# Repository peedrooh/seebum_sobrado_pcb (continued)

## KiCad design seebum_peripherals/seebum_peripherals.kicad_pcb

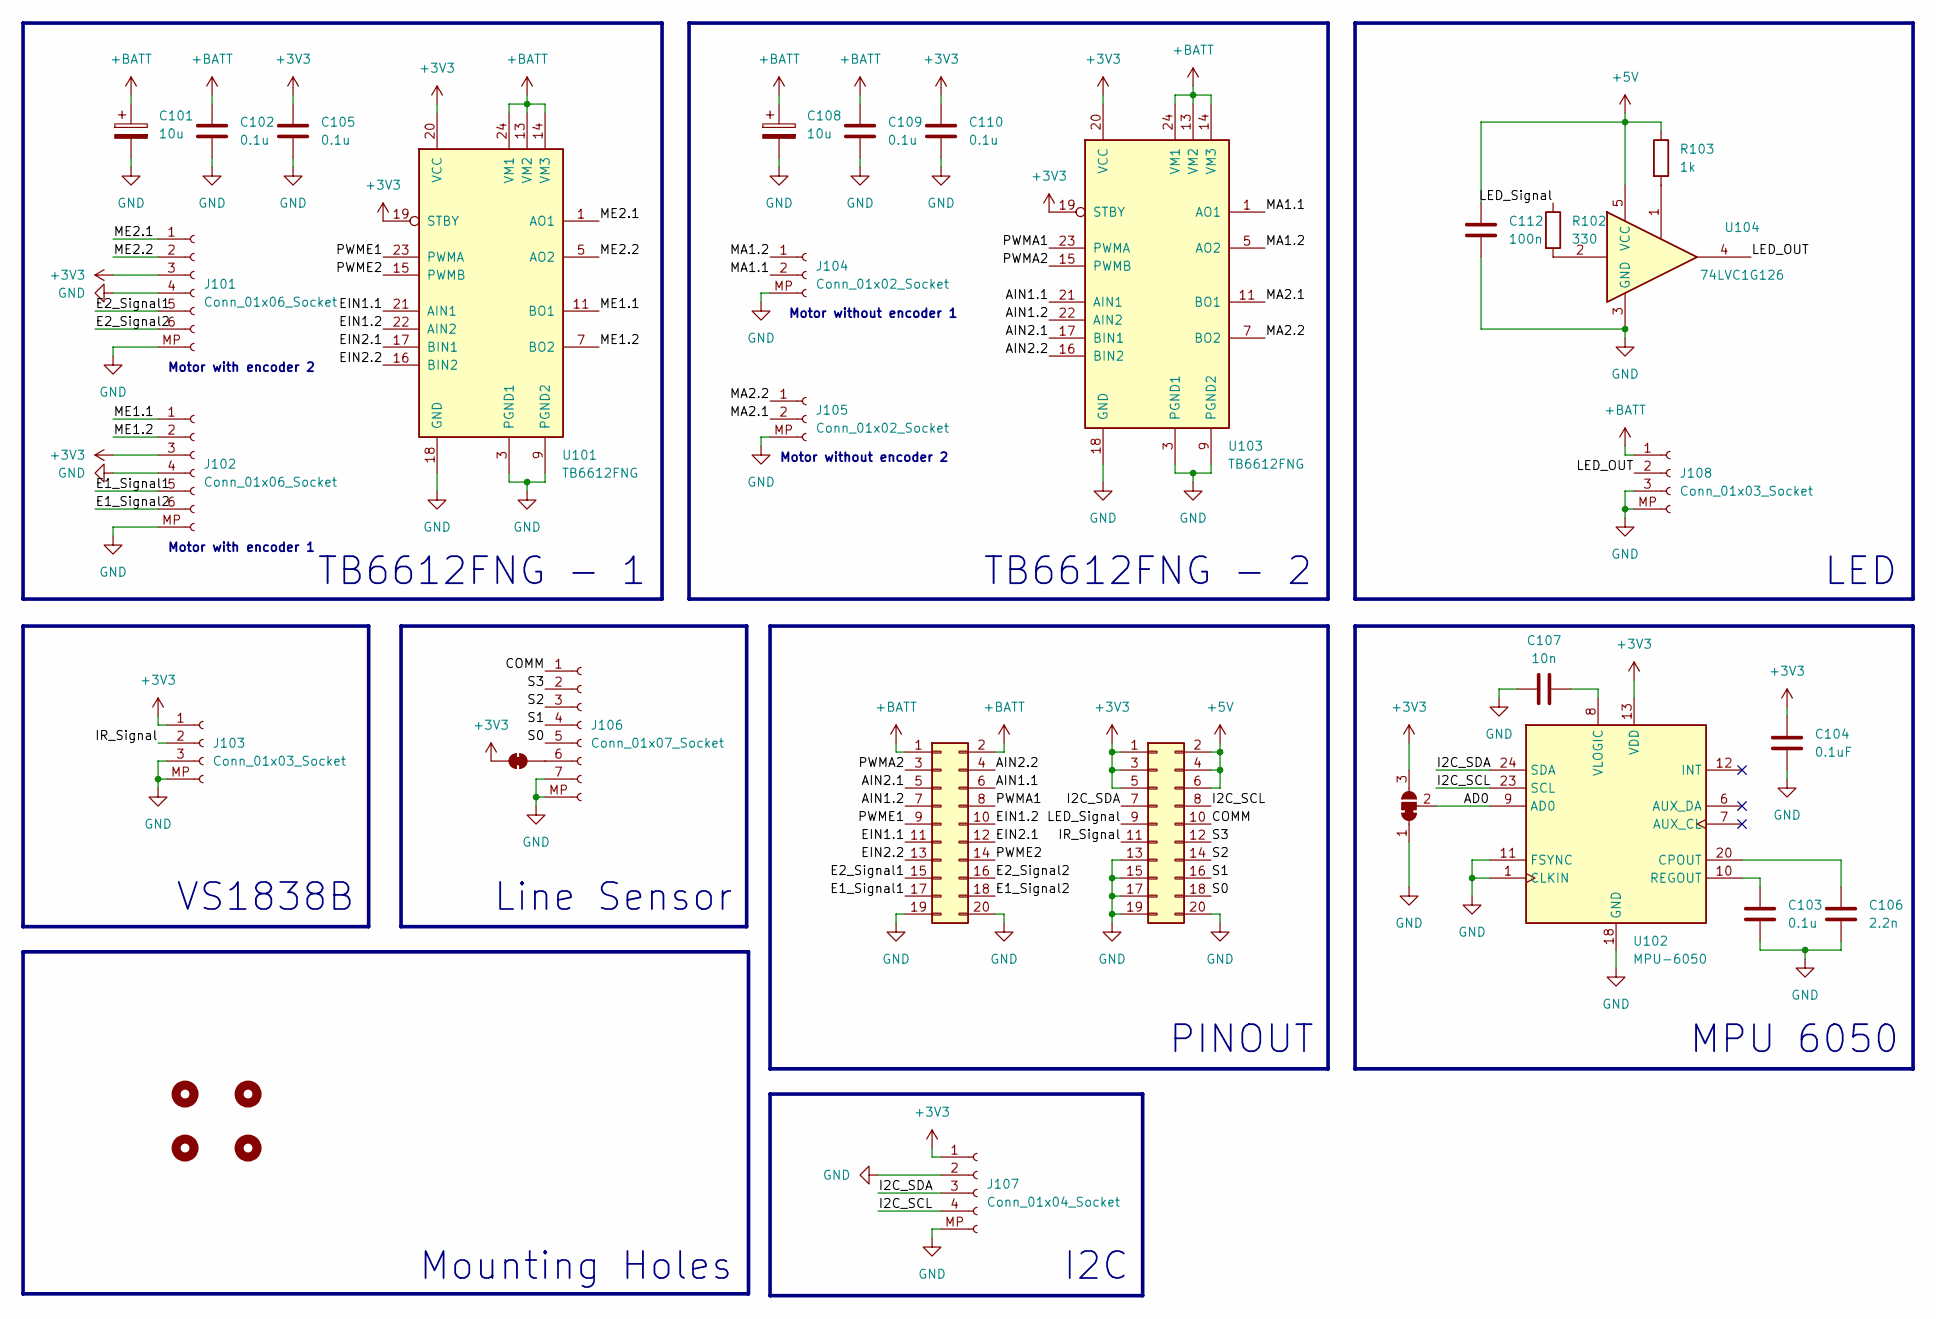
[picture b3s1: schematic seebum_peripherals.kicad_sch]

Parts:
C101, C108: 10u; CP_EIA-3528-21_Kemet-B; LCSC C163225
C102, C103, C105, C109, C110: 0.1u; C_0805_2012Metric; LCSC C38141
C104: 0.1uF; C_0805_2012Metric; LCSC C38141
C106: 2.2n; C_0805_2012Metric; LCSC C36576
C107: 10n; C_0805_2012Metric; LCSC C36576
C112: 100n; C_0805_2012Metric; LCSC C38141
H101, H102, H103, H104: MountingHole; M2.5M3
J101, J102: Conn_01x06_Socket; JST_PH_B6B-PH-SM4-TB_1x06-1MP_P2.00mm_Vertical; LCSC C265088
J103, J108: Conn_01x03_Socket; JST_PH_B3B-PH-SM4-TB_1x03-1MP_P2.00mm_Vertical; LCSC C160353
J104, J105: Conn_01x02_Socket; JST_PH_B2B-PH-SM4-TB_1x02-1MP_P2.00mm_Vertical; LCSC C160352
J106: Conn_01x07_Socket; JST_PH_B7B-PH-SM4-TB_1x07-1MP_P2.00mm_Vertical; LCSC C495700
J107: Conn_01x04_Socket; JST_PH_B4B-PH-SM4-TB_1x04-1MP_P2.00mm_Vertical
J109, J110: Conn_02x10_Odd_Even; PinSocket_2x10_P2.54mm_Vertical
JP101: SolderJumper_3_Bridged12; SolderJumper-3_P1.3mm_Bridged12_RoundedPad1.0x1.5mm
JP102: SolderJumper_2_Bridged; SolderJumper-2_P1.3mm_Bridged_RoundedPad1.0x1.5mm
R102: 330; R_0805_2012Metric; LCSC C17630
R103: 1k; R_0805_2012Metric; LCSC C17513
U101, U103: TB6612FNG; SSOP-24_5.3x8.2mm_P0.65mm; LCSC C88224
U102: MPU-6050; InvenSense_QFN-24_4x4mm_P0.5mm; LCSC C24112
U104: 74LVC1G126; SOT-23-5; LCSC C7834

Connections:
+3V3: C104.1, C105.1, C110.1, J101.3, J102.3, J103.1, J107.1, J110.1, J110.3, J110.5, JP101.3 (B), JP102.1 (A), U101.19 (STBY), U101.20 (VCC), U102.13 (VDD), U103.19 (STBY), U103.20 (VCC)
+5V: C112.1, J110.2, J110.4, J110.6, R103.1, U104.5 (VCC)
+BATT: C101.1, C102.1, C108.1, C109.1, J108.1, J109.1, J109.2, U101.13 (VM2), U101.14 (VM3), U101.24 (VM1), U103.13 (VM2), U103.14 (VM3), U103.24 (VM1)
/AD0: JP101.2 (C), U102.9 (AD0)
/AIN1.1: J109.6, U103.21 (AIN1)
/AIN1.2: J109.7, U103.22 (AIN2)
/AIN2.1: J109.5, U103.17 (BIN1)
/AIN2.2: J109.4, U103.16 (BIN2)
/COMM: J106.1, J110.10
/E1_Signal1: J102.5, J109.17
/E1_Signal2: J102.6, J109.18
/E2_Signal1: J101.5, J109.15
/E2_Signal2: J101.6, J109.16
/EIN1.1: J109.11, U101.21 (AIN1)
/EIN1.2: J109.10, U101.22 (AIN2)
/EIN2.1: J109.12, U101.17 (BIN1)
/EIN2.2: J109.13, U101.16 (BIN2)
/I2C_SCL: J107.4, J110.8, U102.23 (SCL)
/I2C_SDA: J107.3, J110.7, U102.24 (SDA)
/IR_Signal: J103.2, J110.11
/LED_OUT: J108.2, U104.4
/LED_Signal: J110.9, R102.1
/MA1.1: J104.2, U103.1 (AO1), U103.2 (AO1)
/MA1.2: J104.1, U103.5 (AO2), U103.6 (AO2)
/MA2.1: J105.2, U103.11 (BO1), U103.12 (BO1)
/MA2.2: J105.1, U103.7 (BO2), U103.8 (BO2)
/ME1.1: J102.1, U101.11 (BO1), U101.12 (BO1)
/ME1.2: J102.2, U101.7 (BO2), U101.8 (BO2)
/ME2.1: J101.1, U101.1 (AO1), U101.2 (AO1)
/ME2.2: J101.2, U101.5 (AO2), U101.6 (AO2)
/PWMA1: J109.8, U103.23 (PWMA)
/PWMA2: J109.3, U103.15 (PWMB)
/PWME1: J109.9, U101.23 (PWMA)
/PWME2: J109.14, U101.15 (PWMB)
/S0: J106.5, J110.18
/S1: J106.4, J110.16
/S2: J106.3, J110.14
/S3: J106.2, J110.12
GND: C101.2, C102.2, C103.2, C104.2, C105.2, C106.2, C107.1, C108.2, C109.2, C110.2, C112.2, J101.4, J101.MP (Pin_7), J102.4, J102.MP (Pin_7), J103.3, J103.MP (Pin_4), J104.MP (Pin_3), J105.MP (Pin_3), J106.7, J106.MP (Pin_8), J107.2, J107.MP (Pin_5), J108.3, J108.MP (Pin_4), J109.19, J109.20, J110.13, J110.15, J110.17, J110.19, J110.20, JP101.1 (A), U101.3 (PGND1), U101.4 (PGND1), U101.9 (PGND2), U101.10 (PGND2), U101.18 (GND), U102.1 (CLKIN), U102.11 (FSYNC), U102.18 (GND), U103.3 (PGND1), U103.4 (PGND1), U103.9 (PGND2), U103.10 (PGND2), U103.18 (GND), U104.3 (GND)
unnamed: J106.6, JP102.2 (B)
unnamed: R102.2, U104.2
unnamed: R103.2, U104.1
unnamed: C106.1, U102.20 (CPOUT)
unnamed: C103.1, U102.10 (REGOUT)
unnamed: C107.2, U102.8 (VLOGIC)

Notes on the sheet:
TB6612FNG - 1
VS1838B
Motor with encoder 2
Motor with encoder 1
Mounting Holes
Motor without encoder 2
Motor without encoder 1
LED
Line Sensor
TB6612FNG - 2
MPU 6050
PINOUT
I2C

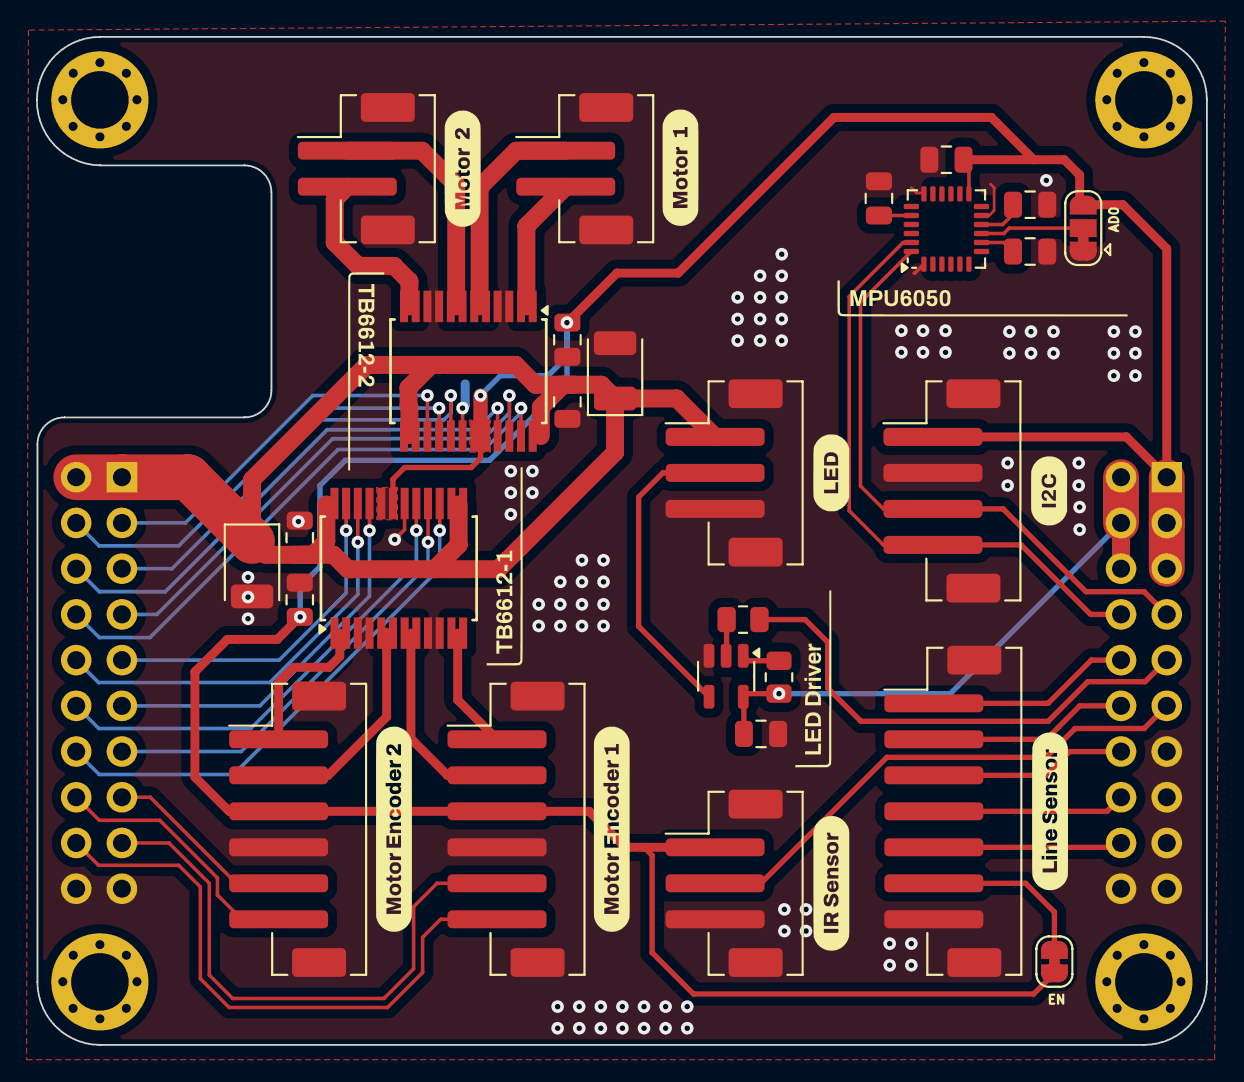
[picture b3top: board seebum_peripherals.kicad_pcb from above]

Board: 2 copper layers, 65.0 x 56.0 mm, 33 parts (0 on the bottom side), 45 nets.

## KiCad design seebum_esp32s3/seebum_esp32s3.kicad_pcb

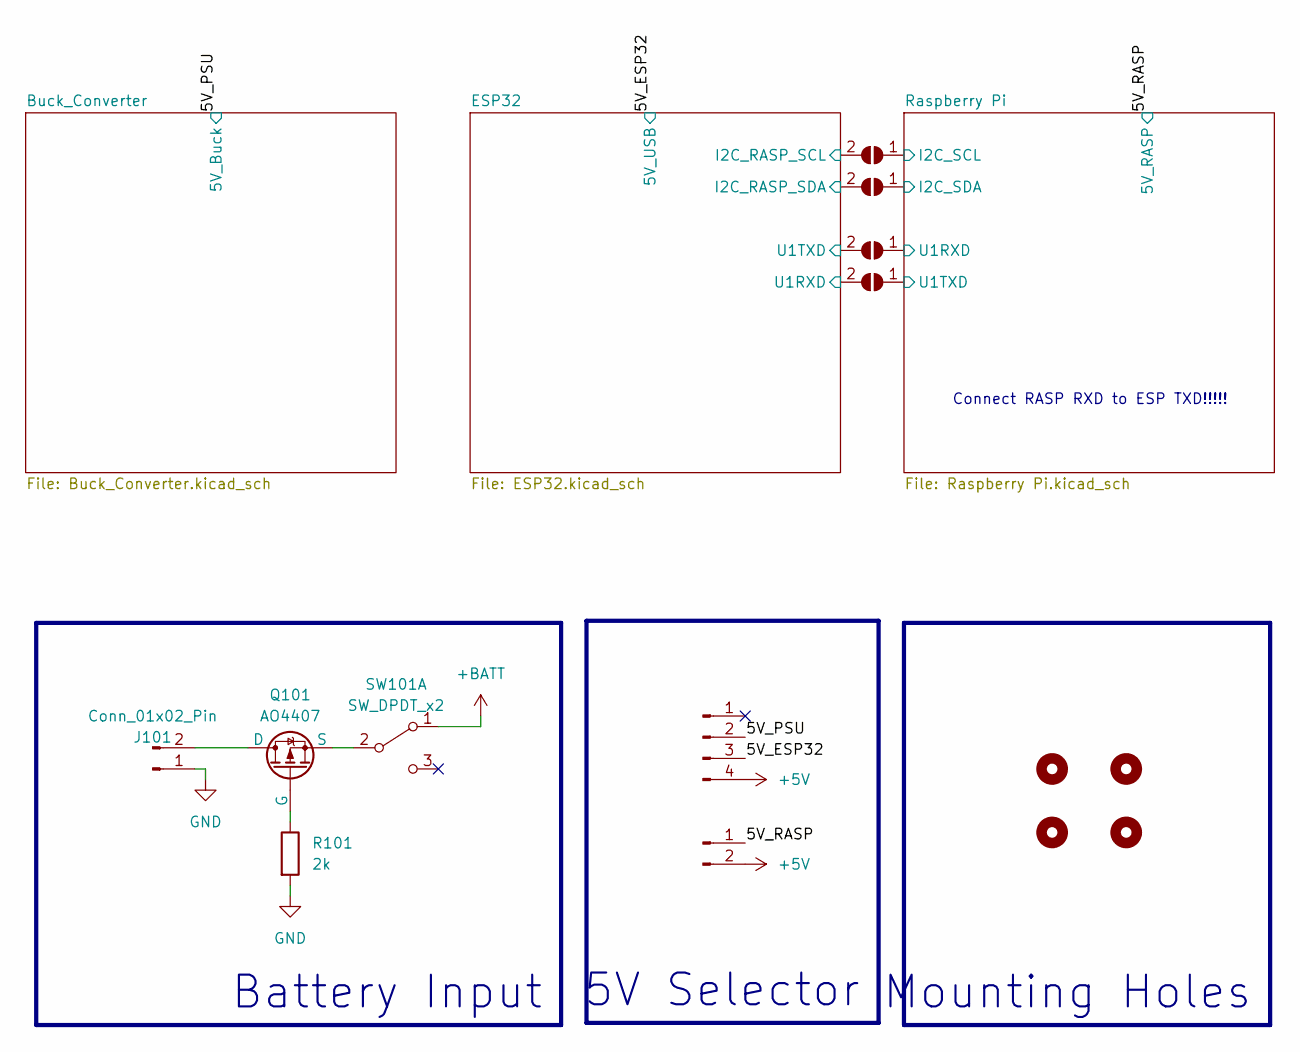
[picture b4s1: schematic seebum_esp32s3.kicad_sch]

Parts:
H101, H102, H103, H104: MountingHole; M2.5M3
J101: Conn_01x02_Pin; AMASS_XT30UPB-M_1x02_P5.0mm_Vertical
J102: Conn_01x04_Pin; PinHeader_2x02_P2.54mm_Vertical
J103: Conn_01x02_Pin; PinHeader_1x02_P2.54mm_Vertical
JP101, JP102: SolderJumper_2_Open; SolderJumper-2_P1.3mm_Open_TrianglePad1.0x1.5mm
JP103, JP104: SolderJumper_2_Open; SolderJumper-2_P1.3mm_Bridged_RoundedPad1.0x1.5mm
Q101: AO4407; SO-8_5.3x6.2mm_P1.27mm; LCSC C469397
R101: 2k; R_0805_2012Metric; LCSC C17604
SW101: SW_DPDT_x2; 5Amp_Switch; LCSC C2884744

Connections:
+5V: J102.4, J103.2; also elsewhere on the board
+BATT: SW101.1 (A); also elsewhere on the board
/5V_ESP32: J102.3; also elsewhere on the board
/5V_PSU: J102.2; also elsewhere on the board
/5V_RASP: J103.1; also elsewhere on the board
/ESP32/GPIO17: JP102.2 (B), JP103.2 (B); also elsewhere on the board
/ESP32/GPIO18: JP101.2 (B), JP104.2 (B); also elsewhere on the board
/Raspberry Pi/RASP_RX: JP103.1 (A); also elsewhere on the board
/Raspberry Pi/RASP_SCL: JP101.1 (A); also elsewhere on the board
/Raspberry Pi/RASP_SDA: JP102.1 (A); also elsewhere on the board
/Raspberry Pi/RASP_TX: JP104.1 (A); also elsewhere on the board
GND: J101.1, R101.2; also elsewhere on the board
unnamed: J101.2, Q101.1 (D)
unnamed: Q101.2 (G), R101.1
unnamed: Q101.3 (S), SW101.2 (B)

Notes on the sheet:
5V Selector
Battery Input
Mounting Holes
Connect RASP RXD to ESP TXD!!!!!

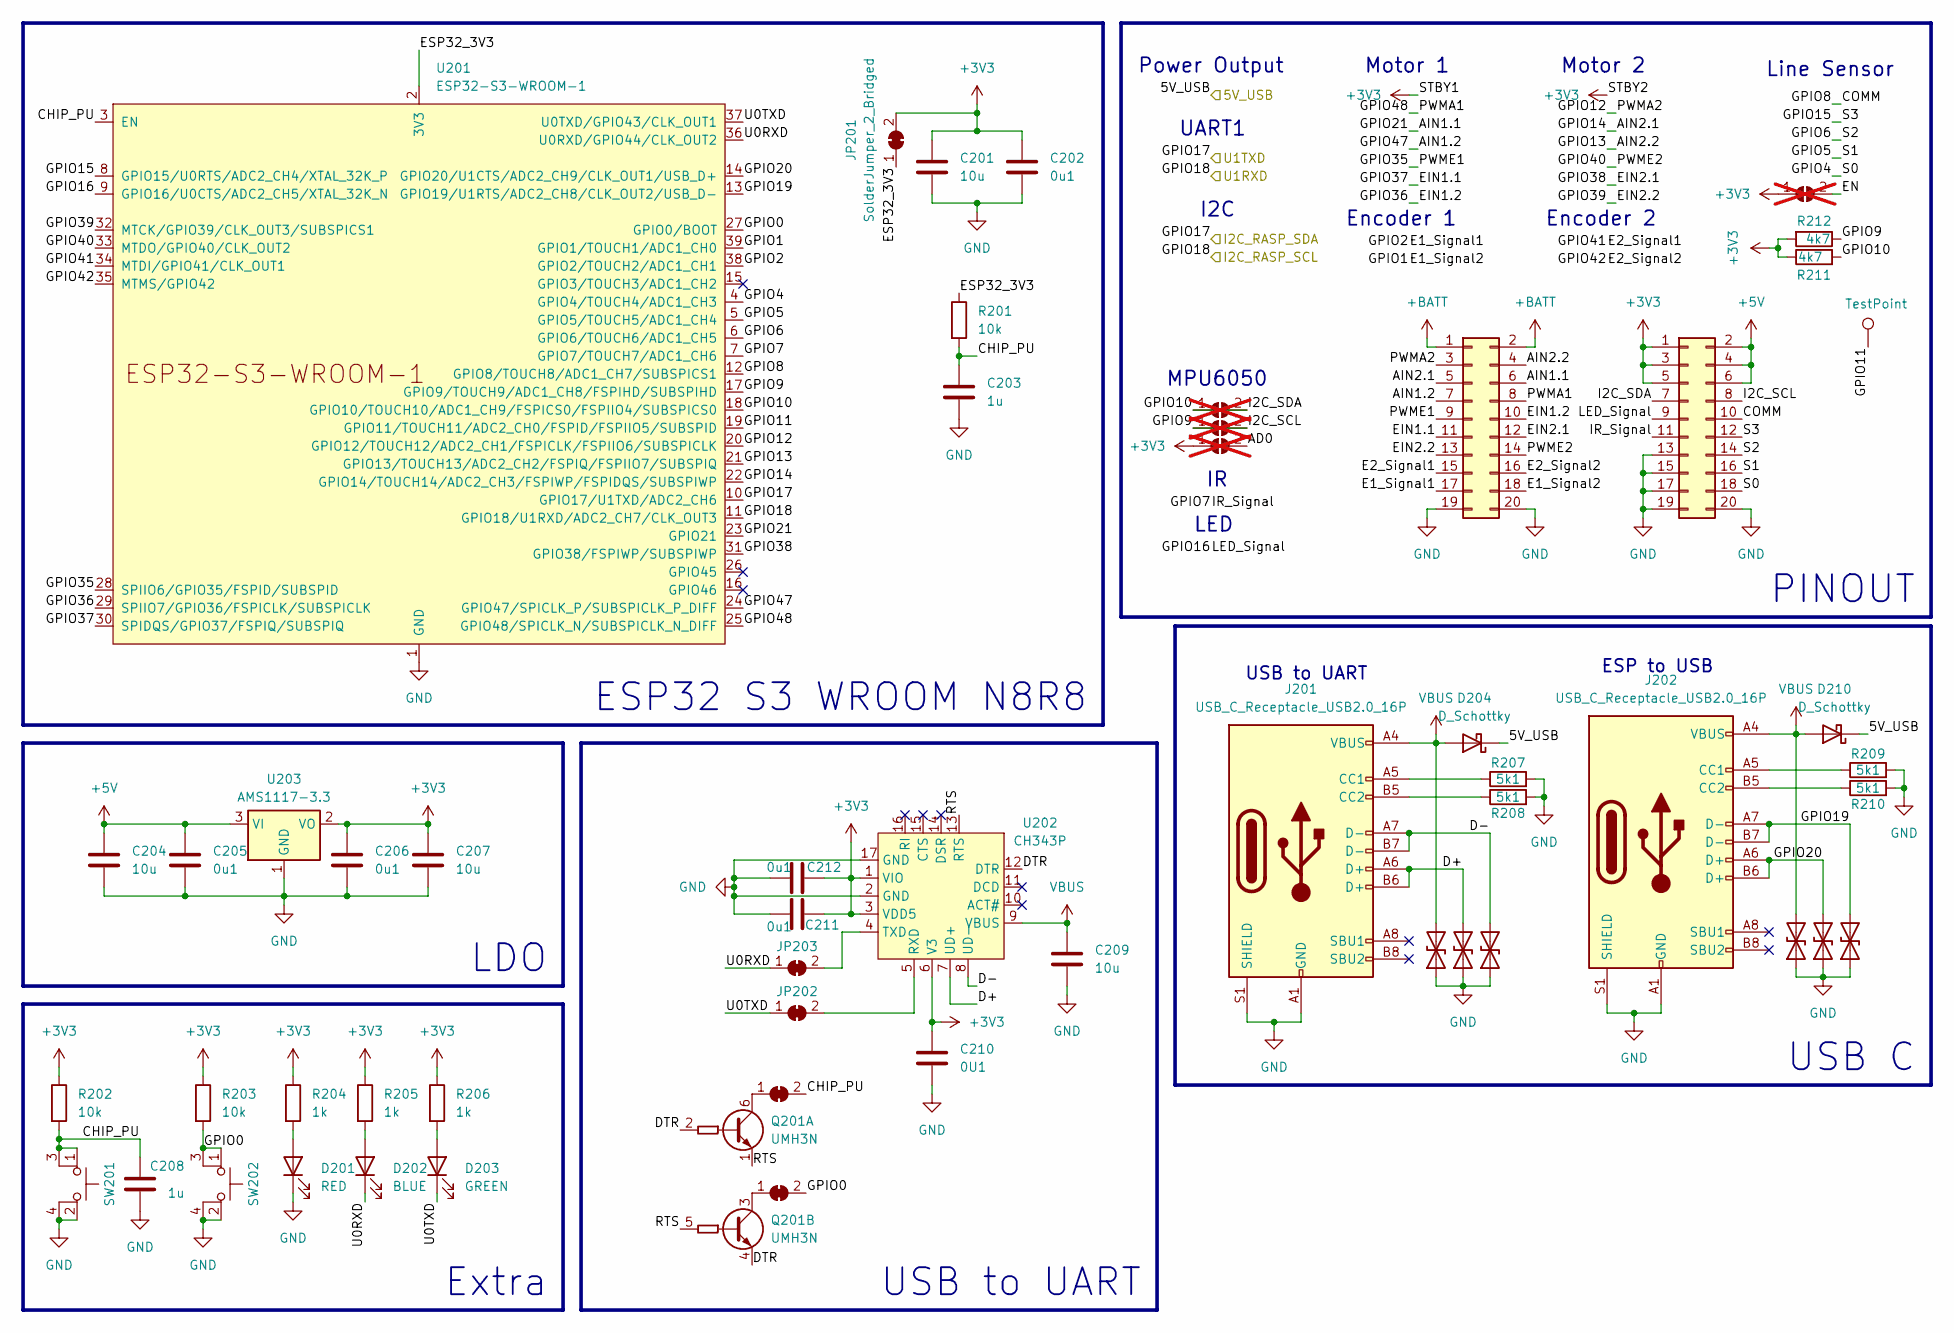
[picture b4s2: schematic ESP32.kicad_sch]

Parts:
C201, C204, C207, C209: 10u; C_0805_2012Metric_Pad1.18x1.45mm_HandSolder
C202, C205, C206, C211, C212: 0u1; C_0805_2012Metric_Pad1.18x1.45mm_HandSolder
C203, C208: 1u; C_0805_2012Metric_Pad1.18x1.45mm_HandSolder
C210: 0U1; C_0805_2012Metric_Pad1.18x1.45mm_HandSolder
D201: RED; LED_0805_2012Metric
D202: BLUE; LED_0805_2012Metric; LCSC C205441
D203: GREEN; LED_0805_2012Metric; LCSC C84260
D204, D210: D_Schottky; D_SOD-323; LCSC C2891705
D205, D206, D207, D208, D209, D211: D_TVS; D_SOD-523; LCSC C383211
J201, J202: USB_C_Receptacle_USB2.0_16P; USB_C_Receptacle_G-Switch_GT-USB-7010ASV; LCSC C2765186
J203, J204: Conn_02x10_Odd_Even; PinHeader_2x10_P2.54mm_Vertical
JP201, JP202, JP203, JP206, JP207: SolderJumper_2_Bridged; SolderJumper-2_P1.3mm_Bridged_RoundedPad1.0x1.5mm
JP204, JP205, JP208, JP209: SolderJumper_2_Open; SolderJumper-2_P1.3mm_Open_TrianglePad1.0x1.5mm; not fitted
Q201: UMH3N; SOT-363_SC-70-6; LCSC C62892
R201, R202, R203: 10k; R_0805_2012Metric_Pad1.20x1.40mm_HandSolder
R204, R205, R206: 1k; R_0805_2012Metric_Pad1.20x1.40mm_HandSolder
R207, R208, R209, R210: 5k1; R_0805_2012Metric_Pad1.20x1.40mm_HandSolder
R211, R212: 4k7; R_0805_2012Metric; LCSC C17673
SW201, SW202: SW_MEC_5E; SW_SPST_B3U-1000P; LCSC C720477
TP201: TestPoint; TestPoint_Pad_D1.0mm
U201: ESP32-S3-WROOM-1; LCSC C2913205
U202: CH343P; TQFN-16-1EP_3x3mm_P0.5mm_EP1.23x1.23mm; LCSC C2846043
U203: AMS1117-3.3; SOT-223-3_TabPin2; LCSC C347222

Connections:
+3V3: C201.1, C202.1, C206.1, C207.1, C210.1, C211.2, C212.2, J204.1, J204.3, J204.5, JP201.2 (B), JP208.1 (A), JP209.1 (A), R202.1, R203.1, R204.1, R205.1, R206.1, R211.1, R212.2, U202.1 (VIO), U202.3 (VDD5), U202.6 (V3), U203.2 (VO); also elsewhere on the board
+5V: C204.1, C205.1, J204.2, J204.4, J204.6, U203.3 (VI); also elsewhere on the board
+BATT: J203.1, J203.2; also elsewhere on the board
/5V_ESP32: D204.1 (K), D210.1 (K); also elsewhere on the board
/ESP32/AIN1.1: J203.6, U201.23 (GPIO21)
/ESP32/AIN1.2: J203.7, U201.24 (GPIO47/SPICLK_P/SUBSPICLK_P_DIFF)
/ESP32/AIN2.1: J203.5, U201.22 (GPIO14/TOUCH14/ADC2_CH3/FSPIWP/FSPIDQS/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)
/ESP32/AIN2.2: J203.4, U201.21 (GPIO13/TOUCH13/ADC2_CH2/FSPIQ/FSPIIO7/S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)
/ESP32/CHIP_PU: C203.1, C208.1, JP206.2 (B), R201.2, R202.2, SW201.1, SW201.3, U201.3 (EN)
/ESP32/COMM: J204.10, U201.12 (GPIO8/TOUCH8/ADC1_CH7/SUBSPICS1)
/ESP32/D+: D206.2 (A2), J201.A6 (D+), J201.B6 (D+), U202.7 (UD+)
/ESP32/D-: D207.2 (A2), J201.A7 (D-), J201.B7 (D-), U202.8 (UD-)
/ESP32/DTR: Q201.2 (B1), Q201.4 (E2), U202.12 (DTR)
/ESP32/E1_Signal1: J203.17, U201.38 (GPIO2/TOUCH2/ADC1_CH1)
/ESP32/E1_Signal2: J203.18, U201.39 (GPIO1/TOUCH1/ADC1_CH0)
/ESP32/E2_Signal1: J203.15, U201.34 (MTDI/GPIO41/CLK_OUT1)
/ESP32/E2_Signal2: J203.16, U201.35 (MTMS/GPIO42)
/ESP32/EIN1.1: J203.11, U201.30 (SPIDQS/GPIO37/FSPIQ/SUBSPIQ)
/ESP32/EIN1.2: J203.10, U201.29 (SPIIO7/GPIO36/FSPICLK/SUBSPICLK)
/ESP32/EIN2.1: J203.12, U201.31 (GPIO38/FSPIWP/SUBSPIWP)
/ESP32/EIN2.2: J203.13, U201.32 (MTCK/GPIO39/CLK_OUT3/SUBSPICS1)
/ESP32/ESP32_3V3: JP201.1 (A), R201.1, U201.2 (3V3)
/ESP32/GPIO0: JP207.2 (B), R203.2, SW202.1, SW202.3, U201.27 (GPIO0/BOOT)
/ESP32/GPIO4: J204.18, U201.4 (GPIO4/TOUCH4/ADC1_CH3)
/ESP32/GPIO5: J204.16, U201.5 (GPIO5/TOUCH5/ADC1_CH4)
/ESP32/GPIO6: J204.14, U201.6 (GPIO6/TOUCH6/ADC1_CH5)
/ESP32/GPIO7: J204.11, U201.7 (GPIO7/TOUCH7/ADC1_CH6)
/ESP32/GPIO9: J204.8, JP205.1 (A), JP205.2 (B), R212.1, U201.17 (GPIO9/TOUCH9/ADC1_CH8/FSPIHD/SUBSPIHD)
/ESP32/GPIO10: J204.7, JP204.1 (A), JP204.2 (B), R211.2, U201.18 (GPIO10/TOUCH10/ADC1_CH9/FSPICS0/FSPIIO4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)
/ESP32/GPIO11: TP201.1, U201.19 (GPIO11/TOUCH11/ADC2_CH0/FSPID/FSPIIO5/S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)
/ESP32/GPIO12: J203.3, U201.20 (GPIO12/TOUCH12/ADC2_CH1/FSPICLK/FSPIIO6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)
/ESP32/GPIO15: J204.12, U201.8 (GPIO15/U0RTS/ADC2_CH4/XTAL_32K_P)
/ESP32/GPIO16: J204.9, U201.9 (GPIO16/U0CTS/ADC2_CH5/XTAL_32K_N)
/ESP32/GPIO17: U201.10 (GPIO17/U1TXD/ADC2_CH6); also elsewhere on the board
/ESP32/GPIO18: U201.11 (GPIO18/U1RXD/ADC2_CH7/CLK_OUT3); also elsewhere on the board
/ESP32/GPIO19: D211.2 (A2), J202.A7 (D-), J202.B7 (D-), U201.13 (GPIO19/U1RTS/ADC2_CH8/CLK_OUT2/USB_D-)
/ESP32/GPIO20: D209.2 (A2), J202.A6 (D+), J202.B6 (D+), U201.14 (GPIO20/U1CTS/ADC2_CH9/CLK_OUT1/USB_D+)
/ESP32/GPIO35: J203.9, U201.28 (SPIIO6/GPIO35/FSPID/SUBSPID)
/ESP32/GPIO40: J203.14, U201.33 (MTDO/GPIO40/CLK_OUT2)
/ESP32/GPIO48: J203.8, U201.25 (GPIO48/SPICLK_N/SUBSPICLK_N_DIFF)
/ESP32/RTS: Q201.1 (E1), Q201.5 (B2), U202.13 (RTS)
/ESP32/U0RXD: D202.1 (K), JP203.1 (A), U201.36 (U0RXD/GPIO44/CLK_OUT2)
/ESP32/U0TXD: D203.1 (K), JP202.1 (A), U201.37 (U0TXD/GPIO43/CLK_OUT1)
GND: C201.2, C202.2, C203.2, C204.2, C205.2, C206.2, C207.2, C208.2, C209.2, C210.2, C211.1, C212.1, D201.1 (K), D205.1 (A1), D206.1 (A1), D207.1 (A1), D208.1 (A1), D209.1 (A1), D211.1 (A1), J201.A1 (GND), J201.A12 (GND), J201.B1 (GND), J201.B12 (GND), J201.S1 (SHIELD), J202.A1 (GND), J202.A12 (GND), J202.B1 (GND), J202.B12 (GND), J202.S1 (SHIELD), J203.19, J203.20, J204.13, J204.15, J204.17, J204.19, J204.20, R207.2, R208.2, R209.2, R210.2, SW201.2, SW201.4, SW202.2, SW202.4, U201.1 (GND), U201.40 (GND), U201.41 (GND), U202.2 (GND), U202.17 (GND), U203.1 (GND); also elsewhere on the board
unnamed: D201.2 (A), R204.2
unnamed: D202.2 (A), R205.2
unnamed: D203.2 (A), R206.2
unnamed: J201.A5 (CC1), R207.1
unnamed: J201.B5 (CC2), R208.1
unnamed: J202.A5 (CC1), R209.1
unnamed: J202.B5 (CC2), R210.1
unnamed: JP202.2 (B), U202.5 (RXD)
unnamed: JP203.2 (B), U202.4 (TXD)
unnamed: JP206.1 (A), Q201.6 (C1)
unnamed: JP207.1 (A), Q201.3 (C2)
VBUS: C209.1, D204.2 (A), D205.2 (A2), D208.2 (A2), D210.2 (A), J201.A4 (VBUS), J201.A9 (VBUS), J201.B4 (VBUS), J201.B9 (VBUS), J202.A4 (VBUS), J202.A9 (VBUS), J202.B4 (VBUS), J202.B9 (VBUS), U202.9 (VBUS)

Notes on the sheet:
USB to UART
UART1
Encoder 1
Line Sensor
I2C
Motor 2
PINOUT
MPU6050
USB C
ESP to USB
Motor 1
ESP32 S3 WROOM N8R8
Power Output
LED
Extra
Encoder 2
LDO

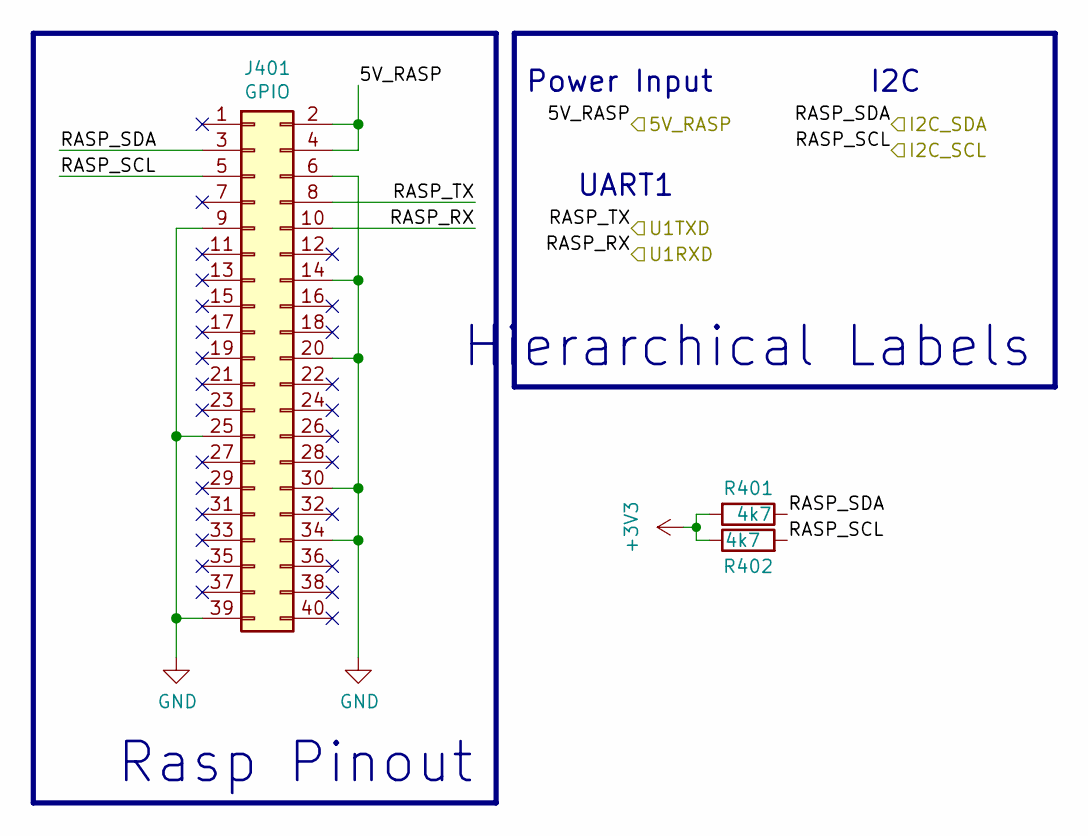
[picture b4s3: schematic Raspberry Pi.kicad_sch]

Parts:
J401: GPIO; PinSocket_2x20_P2.54mm_Vertical
R401, R402: 4k7; R_0805_2012Metric; LCSC C17673

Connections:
+3V3: R401.2, R402.1; also elsewhere on the board
/5V_RASP: J401.2, J401.4; also elsewhere on the board
/Raspberry Pi/RASP_RX: J401.10; also elsewhere on the board
/Raspberry Pi/RASP_SCL: J401.5, R402.2; also elsewhere on the board
/Raspberry Pi/RASP_SDA: J401.3, R401.1; also elsewhere on the board
/Raspberry Pi/RASP_TX: J401.8; also elsewhere on the board
GND: J401.6, J401.9, J401.14, J401.20, J401.25, J401.30, J401.34, J401.39; also elsewhere on the board

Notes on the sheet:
I2C
UART1
Rasp Pinout
Power Input
Hierarchical Labels

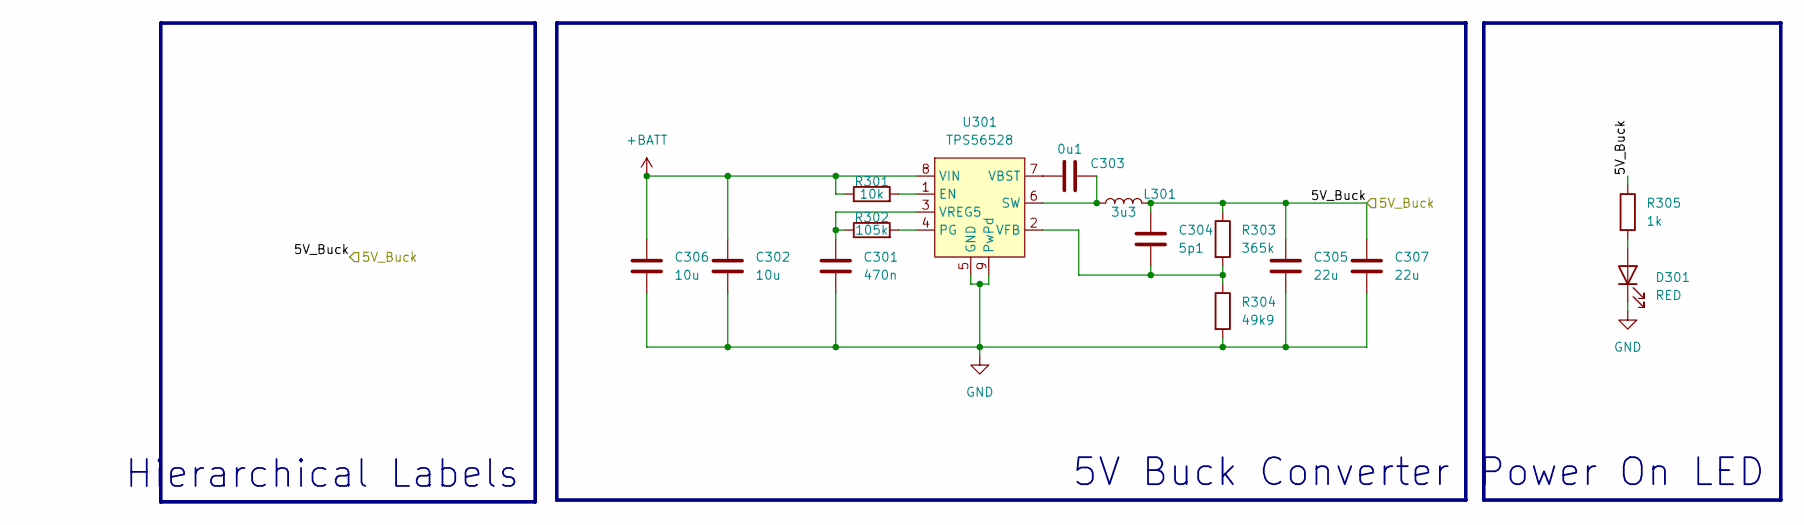
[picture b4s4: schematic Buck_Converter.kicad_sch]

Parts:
C301: 470n; C_0805_2012Metric_Pad1.18x1.45mm_HandSolder
C302: 10u; C_1210_3225Metric_Pad1.33x2.70mm_HandSolder
C303: 0u1; C_0805_2012Metric_Pad1.18x1.45mm_HandSolder
C304: 5p1; C_0805_2012Metric_Pad1.18x1.45mm_HandSolder
C305, C307: 22u; C_0805_2012Metric_Pad1.18x1.45mm_HandSolder
C306: 10u; C_1210_3225Metric_Pad1.33x2.70mm_HandSolder; LCSC C2918502
D301: RED; LED_0805_2012Metric
L301: 3u3; L_Bourns_SRP1050WA; LCSC C497894
R301: 10k; R_0805_2012Metric_Pad1.20x1.40mm_HandSolder
R302: 105k; R_0805_2012Metric_Pad1.20x1.40mm_HandSolder; LCSC C3000727
R303: 365k; R_0805_2012Metric_Pad1.20x1.40mm_HandSolder; LCSC C2999471
R304: 49k9; R_0805_2012Metric_Pad1.20x1.40mm_HandSolder; LCSC C17719
R305: 1k; R_0805_2012Metric_Pad1.20x1.40mm_HandSolder
U301: TPS56528; Texas_HSOP-8-1EP_3.9x4.9mm_P1.27mm_ThermalVias; LCSC C138716

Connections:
+BATT: C302.1, C306.1, R301.1, U301.8 (VIN); also elsewhere on the board
/5V_PSU: C304.1, C305.1, C307.1, L301.2, R303.1, R305.1; also elsewhere on the board
GND: C301.2, C302.2, C305.2, C306.2, C307.2, D301.1 (K), R304.2, U301.5 (GND), U301.9 (PwPd); also elsewhere on the board
unnamed: D301.2 (A), R305.2
unnamed: R301.2, U301.1 (EN)
unnamed: R302.2, U301.4 (PG)
unnamed: C303.2, L301.1, U301.6 (SW)
unnamed: C303.1, U301.7 (VBST)
unnamed: C304.2, R303.2, R304.1, U301.2 (VFB)
unnamed: C301.1, R302.1, U301.3 (VREG5)

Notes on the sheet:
Power On LED
5V Buck Converter
Hierarchical Labels

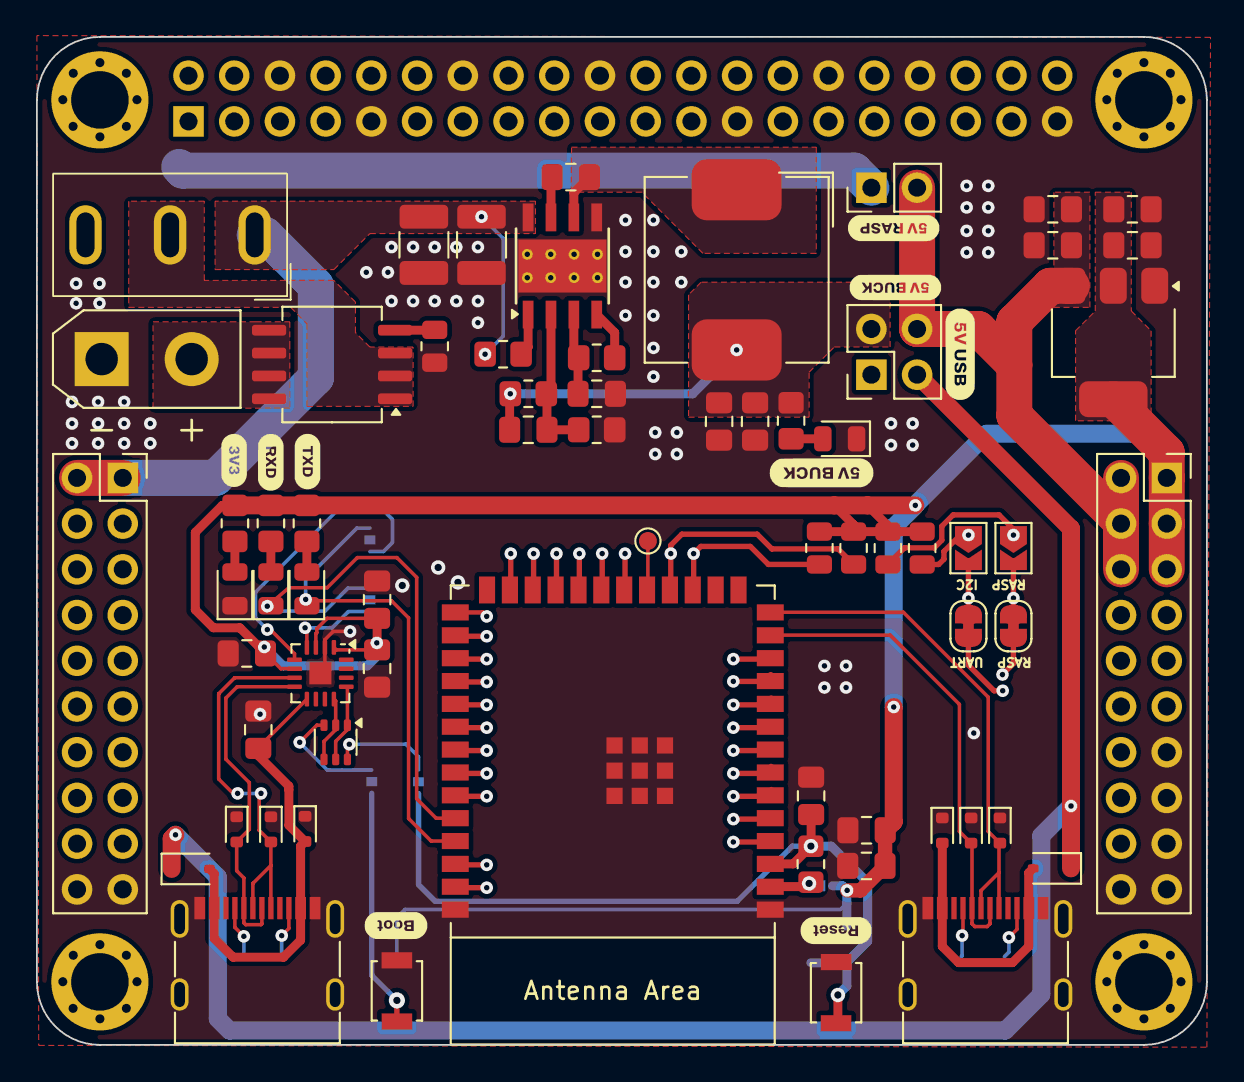
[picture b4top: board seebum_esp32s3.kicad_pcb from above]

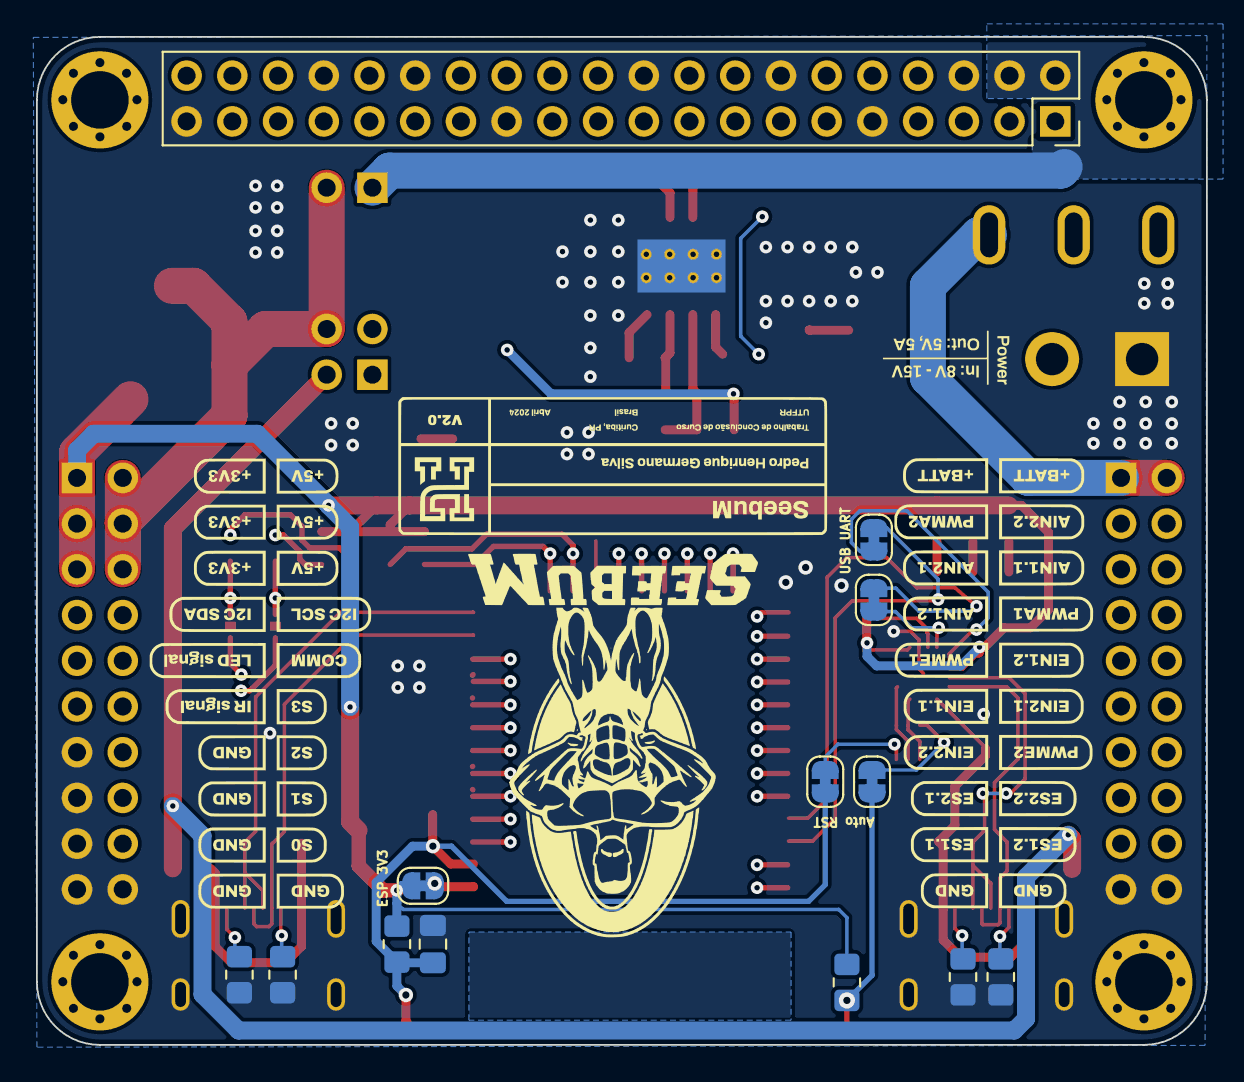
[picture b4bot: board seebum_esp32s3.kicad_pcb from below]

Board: 4 copper layers, 65.0 x 56.0 mm, 83 parts (15 on the bottom side), 72 nets.

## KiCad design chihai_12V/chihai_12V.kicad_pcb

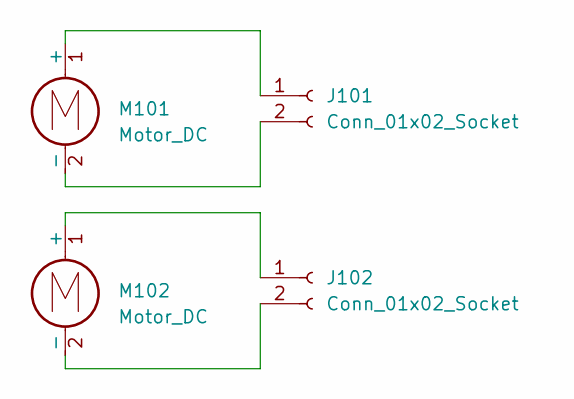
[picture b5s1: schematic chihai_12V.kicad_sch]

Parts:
J101, J102: Conn_01x02_Socket; JST_PH_S2B-PH-SM4-TB_1x02-1MP_P2.00mm_Horizontal
M101, M102: Motor_DC; Chihai_CHR_GM16

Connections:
unnamed: J101.1, M101.1 (+)
unnamed: J101.2, M101.2 (-)
unnamed: J102.1, M102.1 (+)
unnamed: J102.2, M102.2 (-)

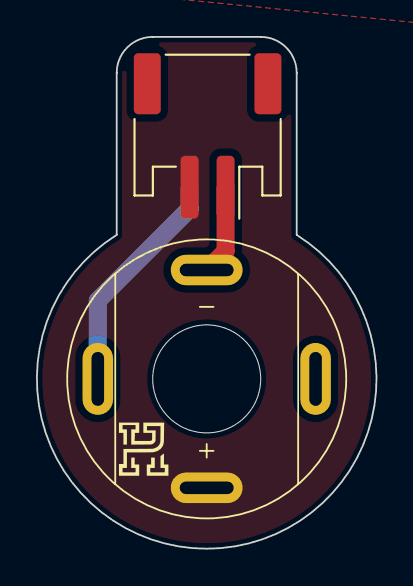
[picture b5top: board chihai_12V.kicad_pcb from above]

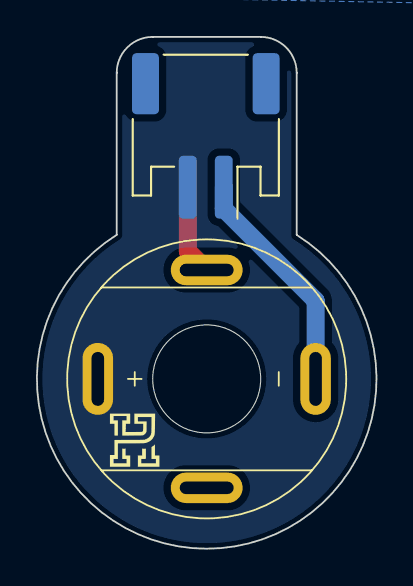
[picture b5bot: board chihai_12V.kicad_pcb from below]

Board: 2 copper layers, 18.9 x 28.4 mm, 4 parts (2 on the bottom side), 4 nets.

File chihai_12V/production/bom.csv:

Designator,Footprint,Quantity,Value,LCSC Part #
J101,JST_PH_B2B-PH-K_1x02_P2.00mm_Vertical,1,Conn_01x02_Socket,
M101,Chihai_CHR_GM16,1,Motor_DC,

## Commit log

2024-04-23 Feat: add double chihai PCB
2024-04-23 Remove chihai
2024-04-23 Feat: some improvments
2024-04-23 ahhh
2024-04-23 last try
2024-04-26 Feat: remove backup files and other from git
2024-04-26 Feat: fix uart1 schematic issue and I2C redundancy
2024-04-26 Feat: fix I2C and silkscreen
2024-04-26 Feat: fabrication files using JLCPCB plugin
2024-04-28 Feat: I2C and UART to same pins in ESP32, since any GPIO can be RxD and TxD
2024-05-30 Feat: final revision
2024-08-12 Remove old PCB
2024-08-12 Feat: add version 3
2024-08-12 Feat: add PCB 3D model
